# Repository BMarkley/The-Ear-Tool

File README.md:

# Modification of The Ear Tool by Harbin Repairs, to use materials I had available for the build. Optimized for ordering from JLCPCB. Moved the amplifier near the signal source to reduce crosstalk.
-Brian Markley EIT RSE

# The Ear Tool

Model: ET-1

Get this kit at our store: http://bit.ly/2TQ3Cbr
Or on eBay: https://ebay.to/38sRZv4

# License
Harbin Repairs 2020
Creative Commons Attribution ShareAlike 4.0
https://creativecommons.org/licenses/by-sa/4.0/

# Documentation

## What is the Ear tool?
The Ear tool can be used to detect almost any electromagnetic interference coming from your electronics such as a power supply, transformer, CPU, microcontroller, wireless transmitter, relays, switches, speakers, transducers, transistors and more. At Harbin Repairs we use the Ear Tool to diagnose problems with computer motherboards, cellphones, and televisions by pointing the tool at different parts of a circuit board and listening to the high frequency pulsing coming from different components. For example, this can help us determine if a CPU or microcontroller is doing any processing or if it’s just sitting there burning up because there’s a short somewhere. It can also let us know if a cellphone or other device is turning on even if there’s no sign of life on the screen or lights. The tool can also be used to discover the different noises your electronics make when they are doing different things (e.g. standby mode vs. fully powered on). For the controls, the gain switch adjusts between high and low sensor gain and the full scope switch switch is used to help clear up some of the background noise. More examples are in the assembly guide video below.
## Demonstration and kit assmebly guide Video

https://youtu.be/0QIx8OhJN-o

## Bill of Materials

| Description                   | Part #             | Main Links (Affiliate)      | eBay Links (Affiliate)  | Amazon Links (Affiliate) |
|-------------------------------|--------------------|-----------------------------|-------------------------|--------------------------|
| PCB                           | N/A                | PCB manufacturer of choice  | N/A                     | N/A                      |
| Enclosure                     | 1591BSBK           | https://bit.ly/2sKEk3i      | https://ebay.to/30SXp05 | https://amzn.to/2um65Qa  |
| Speaker                       | 1.5W8R 8R1.5W      | https://bit.ly/2upP8nP      | https://ebay.to/36eXlbX | N/A                      |
| 100Ω Resistor 0805            | N/A                | https://bit.ly/2TKRSqF      | https://ebay.to/2ul6eDt | N/A                      |
| 1kΩ Resistor 0805             | N/A                | https://bit.ly/36lOaql      | https://ebay.to/2TNRTtY | N/A                      |
| 220uf Electrolytic Capacitor  | N/A                | https://bit.ly/2RxIeEY      | https://ebay.to/2RHrTh0 | N/A                      |
| 4.7uf Ceramic Capacitor 0805  | N/A                | https://bit.ly/3awu9k3      | https://ebay.to/36lOJ3r | N/A                      |
| Blue LED 5mm                  | N/A                | https://bit.ly/2GgnU5K      | https://ebay.to/37h1f5p | https://amzn.to/37sNP6c  |
| LM386 Audio Amp               | LM386              | https://bit.ly/2tweNeR      | https://ebay.to/2RHXmA1 | N/A                      |
| SPST Slide Switch THT         | SS12F17G4          | https://bit.ly/30IrAqm      | https://ebay.to/30MXx14 | N/A                      |
| 3.5mm Headphone Jack          | 307 3F07           | https://bit.ly/36hQ5Mu      | https://ebay.to/36eJQcm | https://amzn.to/36eYmRj  |
| 100mH Inductor                | N/A                | https://bit.ly/38xpU63      | https://ebay.to/36eJQJo | https://amzn.to/2TNTjoi  |
| Felt Tape                     | JVCC FELT-065      | https://ebay.to/2G9WzlS     | https://ebay.to/2G9WzlS | https://amzn.to/30JB05h  |
| Battery Compartment Separator | Custom Laser Cut   | https://www.delviesplastics.com/ | Drawings available on Github | N/A                      |
| 9v Battery Clip               | N/A                | https://bit.ly/2RfzFjh      | https://ebay.to/2uis6zx | https://amzn.to/2TKSEnB  |
| 10KΩ Potentiometer            | B103 10K 0932 WH09 | https://bit.ly/2ul666X      | https://ebay.to/2NRkgno | N/A                      |
| Pot Knob 15mm x 17mm x 6mm    | N/A                | https://bit.ly/37f6bYo      | https://ebay.to/37jvYim | https://amzn.to/2GawAur  |
| Terminal Block Connector      | KF301-5.0-2P       | https://bit.ly/38xsJnF      | https://ebay.to/3avkOZG | https://amzn.to/369tQZ2  |

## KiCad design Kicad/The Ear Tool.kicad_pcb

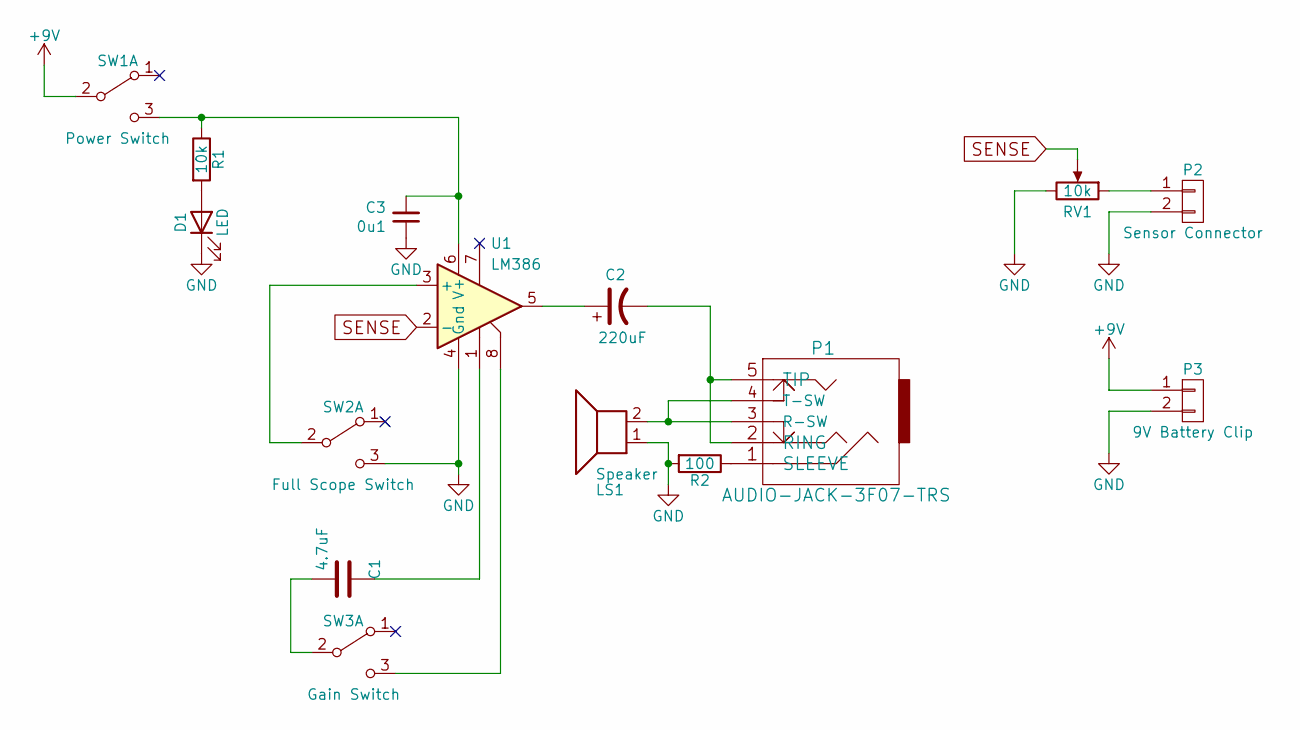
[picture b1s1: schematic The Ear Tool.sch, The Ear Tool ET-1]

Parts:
C1: 4.7uF; C_0603_1608Metric
C2: 220uF; CP_Elec_6.3x7.7
C3: 0u1; C_0603_1608Metric
D1: LED; LED_D5.0mm_Clear
LS1: Speaker; Surface Connector
P1: AUDIO-JACK-3F07-TRS
P2: Sensor Connector; TerminalBlock_RND_205-00232_Pitch5.08mm
P3: 9V Battery Clip; Surface Connector
R1: 10k; R_0603_1608Metric
R2: 100; R_0603_1608Metric
RV1: 10k; Potentiometer_Bourns_PTV09A-1_Single_Vertical
SW1: Power Switch; SPDT_generic_toggle
SW2: Full Scope Switch; SPDT_generic_toggle
SW3: Gain Switch; SPDT_generic_toggle
U1: LM386; SOIC-8-N

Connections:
+9V: P3.1, SW1.2 (B)
GND: C3.1, D1.1 (K), LS1.1, P2.2, P3.2, R2.2, RV1.3, SW2.3 (C), U1.4 (Gnd)
unnamed: C1.1, U1.1
unnamed: C1.2, SW3.2 (B)
unnamed: C2.1, U1.5
unnamed: C2.2, P1.2 (RING), P1.5 (TIP)
unnamed: C3.2, R1.1, SW1.3 (C), U1.6 (V+)
unnamed: D1.2 (A), R1.2
unnamed: LS1.2, P1.3 (R-SW), P1.4 (T-SW)
unnamed: P1.1 (SLEEVE), R2.1
unnamed: P2.1, RV1.1
unnamed: SW2.2 (B), U1.3 (+)
unnamed: SW3.3 (C), U1.8
SENSE: RV1.2, U1.2 (-)

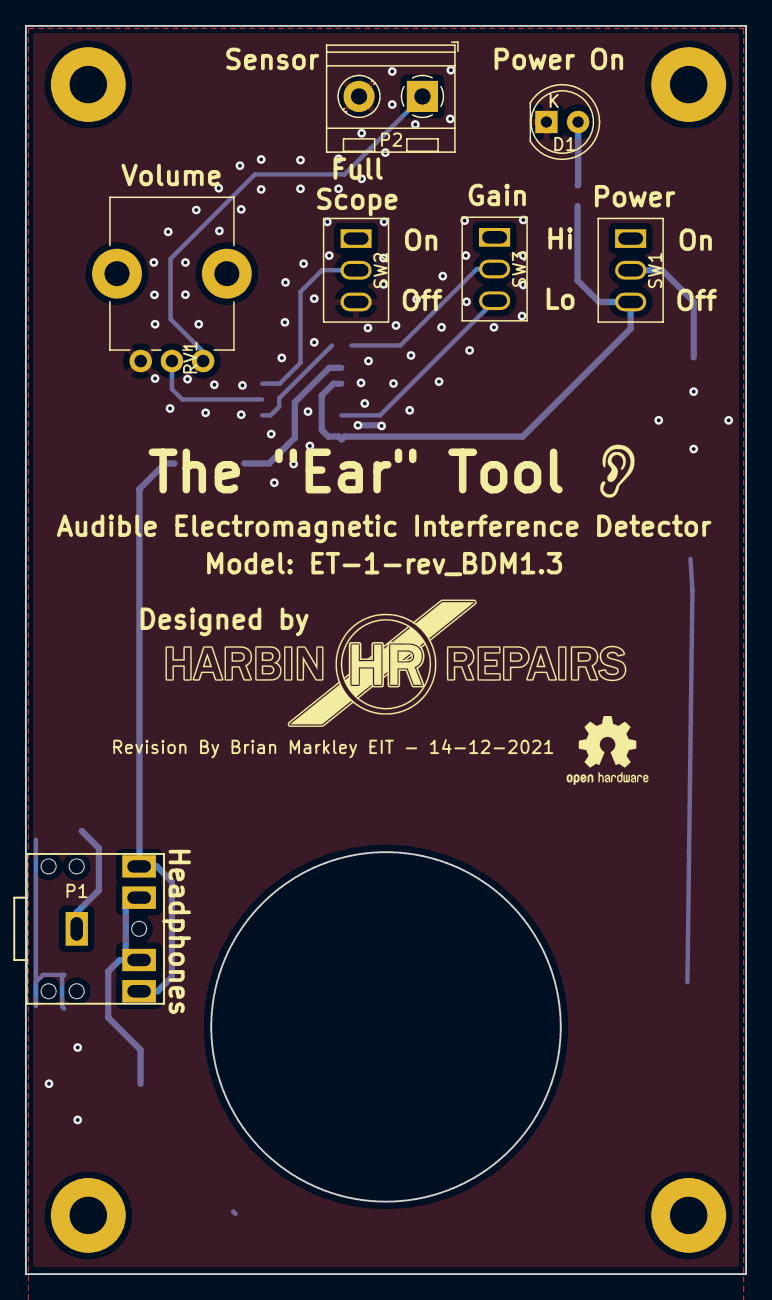
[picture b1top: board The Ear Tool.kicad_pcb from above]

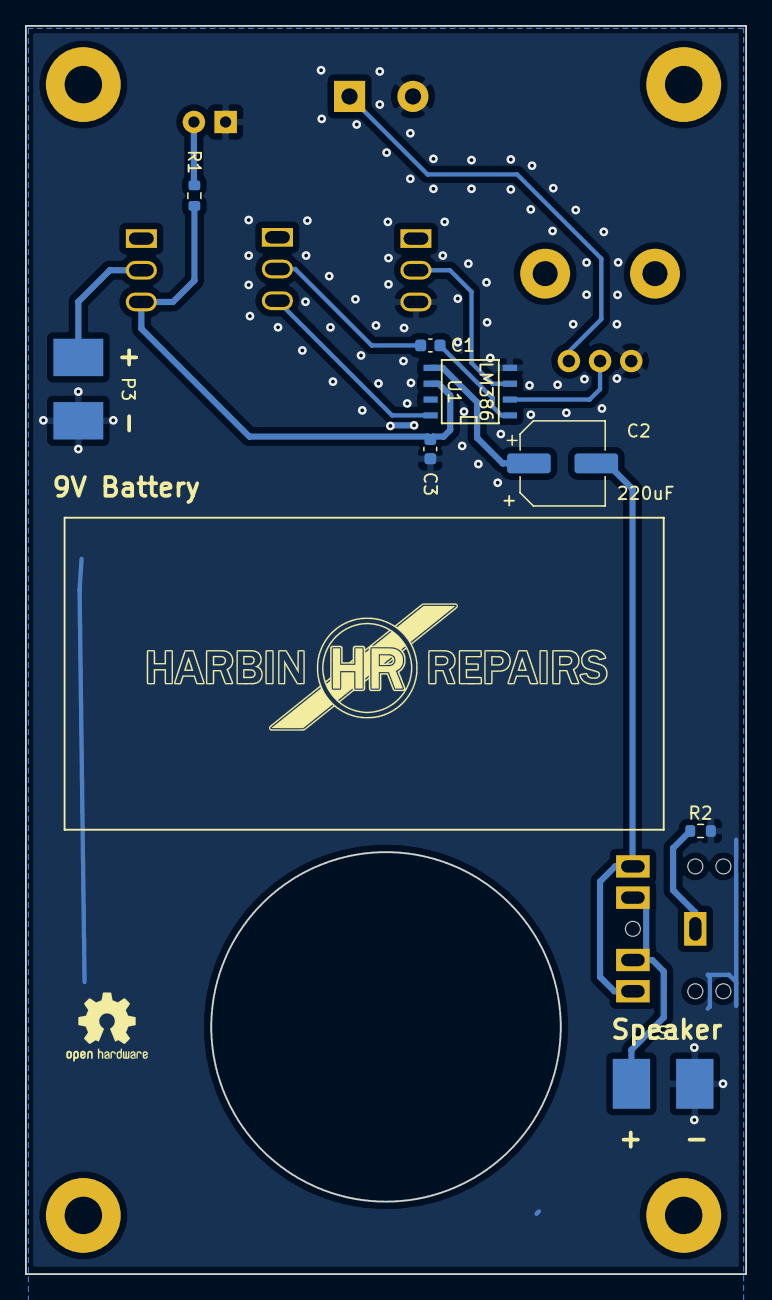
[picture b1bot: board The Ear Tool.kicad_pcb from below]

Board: 2 copper layers, 57.7 x 100.0 mm, 22 parts (9 on the bottom side), 14 nets.

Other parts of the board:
G1, G2: LOGO; HR_LOGO_37.4x10.6mm
G3: LOGO; Ear_icon_4.2x4.2mm
M1, M2, M3, M4: MountingHole_3mm_Pad
